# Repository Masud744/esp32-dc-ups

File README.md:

# esp32-dc-ups

> **Zero-Reboot DC UPS for ESP32 & IoT — Seamless 0ms power-path switching, wide DC input (6.5V–24V), 1S Li-ion battery backup, and dual regulated 5.0V & 3.3V outputs in KiCad.**

An industrial-grade, ultra-low-cost, uninterruptible power supply (DC UPS) module designed from the ground up to prevent brownout crashes and reboot loops on ESP32, ESP8266, Raspberry Pi Pico, and sensitive IoT sensor nodes. Designed in **KiCad 10** with 100% verified Design Rule Checks (DRC) and Electrical Rule Checks (ERC).

---

## 3D Hardware Previews

| Isometric View | Top View |
| :---: | :---: |
|  |  |

---

## Why esp32-dc-ups?

Most DIY IoT backup solutions connect a single 18650 lithium battery directly to an ESP32's `VIN` or rely on simple diode-ORing circuits. In production deployments, this leads to two major failure modes:

### 1. The "AMS1117 LDO Dropout Trap"
Over 90% of budget ESP32 development boards (NodeMCU-32S, ESP32-WROOM DevKit) use the **AMS1117-3.3** linear regulator, which has a dropout voltage ($V_{drop}$) of **$1.1\text{V} - 1.3\text{V}$** under typical Wi-Fi transmission bursts ($300\text{mA} - 500\text{mA}$):
$$V_{IN(min)} = 3.3\text{V} + 1.1\text{V} = 4.4\text{V}$$
* A standard single-cell Li-ion battery discharges from **$4.2\text{V} \rightarrow 3.0\text{V}$** (nominal $3.7\text{V}$).
* When battery voltage dips below $4.0\text{V}$, the AMS1117's output drops below $2.8\text{V}$, instantly tripping the ESP32 internal brownout detector (BOD) and causing infinite reboot loops.

### 2. Li-ion Charger Never Terminates
Powering an active IoT microcontroller directly across a charging TP4056 module causes continuous load current ($>70\text{mA}$) to draw through the battery pins. The TP4056 never detects the $C/10$ termination threshold, causing perpetual float charging, battery swelling, plating, and thermal hazards.

### The Solution: True 3-Stage Isolated Power-Path

| Feature | Standard USB / Diode ORing | Commercial Power Banks | **esp32-dc-ups (This Project)** |
| :--- | :---: | :---: | :---: |
| **Switchover Delay** | $>10\text{ms}$ (Reboots ESP) | $50\text{ms} - 200\text{ms}$ (Full Reboot) | **$0\text{ms}$ (Zero Delay, Anti-Reboot)** |
| **Input Voltage Range** | $5.0\text{V} \pm 5\%$ only | $5.0\text{V}$ only | **$6.5\text{V} - 24.0\text{V}$ Wide DC** |
| **Reverse Polarity Protection** | Rare / None | Fuse / None | **1N5822 3A Schottky Protected** |
| **Li-ion Termination ($C/10$)** | Broken (Continuous load) | Internal BMS | **Fully Isolated (Load never touches battery during mains)** |
| **Dual Regulated Rails** | No | 5V only | **5.0V (Boost 2A) + 3.3V (LDO) on Screw Terminals** |
| **Build Cost** | BDT 300 | BDT 1,200 – 1,800 | **BDT 430 – 490 (~$4 USD)** |

---

## Key Features

1. **Wide DC Input Stage (6.5V – 24V):**
   - High-current 5.08mm screw terminal (`J1`).
   - Integrated reverse-polarity protection via **1N5822 (3A / 40V Schottky)**.
   - Dual-stage input filter with high-frequency decoupling ($100\mu\text{F} / 35\text{V} + 100\text{nF}$).
   - Steps down any standard adapter ($7.5\text{V}, 9\text{V}, 12\text{V}, 15\text{V}, 19\text{V}, 24\text{V}$) to a clean $5.0\text{V}$ bus via high-efficiency Buck converter headers.

2. **Isolated Safe Charging (TP4056 + DW01A):**
   - System load is completely isolated from the battery charging circuit during mains operation.
   - TP4056 properly reaches its $C/10$ charge cut-off ($4.20\text{V} \pm 1\%$), maximizing cell cycle life.
   - Compatible with any 1S $3.7\text{V}$ 18650 cylindrical cell or Li-Po pouch battery.

3. **Sub-Millisecond Zero-Delay Power-Path Switching:**
   - Active P-Channel MOSFET (**NDP6020P / AO3401**) + Ultra-Fast Dual Schottky Barrier Diode (**MBR460CT**).
   - $10\text{k}\Omega$ pull-down resistor ensures instantaneous gate turn-on when mains voltage drops.
   - Switched intermediate bus backed by a low-ESR bulk capacitance matrix ($220\mu\text{F} + 10\mu\text{F} + 100\text{nF}$) for **$0\text{ms}$ cutover transition**.

4. **Synchronous Dual Regulated Outputs:**
   - **5.0V Rail:** Regulated via MT3608 high-frequency boost converter with a massive **$1000\mu\text{F} / 25\text{V}$ reservoir capacitor** to easily absorb ESP32 Wi-Fi TX current spikes ($>450\text{mA}$).
   - **3.3V Rail:** Dedicated onboard **AMS1117-3.3** linear regulator with thermal via array connecting directly to the bottom solid ground plane.
   - Both rails terminate on dedicated 5.08mm Phoenix-compatible screw terminals.

---

## System Architecture

```
[DC IN 6.5V-24V] ──> [1N5822 Schottky] ──> [Input Buck Module] ──> [+5V_IN Bus]
  (Screw Term J1)      (Reverse Protect)      (Steps down to 5.0V)        │
                                                                         ├──> [TP4056 + DW01A] ──> [1S Li-ion Battery]
                                                                         │       (Isolated Charge)          │
                                                                         │                                  │
[MT3608 Boost 5.1V] <── [Zero-Delay P-MOSFET + MBR460CT Power-Path] <────┴──────────────────────────────────┘
        │
        ├───> [1000uF Reservoir Cap] ───> [5.0V OUT Screw Terminal (J6)]
        │
        └───> [AMS1117-3.3 LDO] ────────> [3.3V OUT Screw Terminal (J7)]
```

---

## Hardware Specifications

| Parameter | Specification | Note |
| :--- | :--- | :--- |
| **Input Voltage Range** | $6.5\text{V} - 24.0\text{V}$ DC | Compatible with 9V/12V/19V/24V adapters |
| **Backup Battery** | Single-cell Li-ion / Li-Po ($3.7\text{V}$ nom, $4.2\text{V}$ max) | 18650, 21700, or flat pouch cell |
| **Output 1 (5V Rail)** | $5.0\text{V} \pm 2\%$ @ up to $2.0\text{A}$ | Primary supply for dev kits, sensors, relays |
| **Output 2 (3.3V Rail)** | $3.3\text{V} \pm 1.5\%$ @ up to $800\text{mA}$ | Direct clean rail for ESP32 SoC, sensors |
| **Cutover Transition Delay** | **$< 0.1\text{ms}$ (Effectively 0ms)** | Microcontroller brownout risk: **0%** |
| **PCB Dimensions** | $105\text{mm} \times 70\text{mm}$ | 2-layer FR4, $1.6\text{mm}$ thickness, 1oz Cu |
| **Mounting Holes** | $4\times \text{M3}$ ($3.2\text{mm}$) | Grounded rings with thermal relief |
| **Terminals** | $3\times 5.08\text{mm}$ 2-Pin Screw Terminals | Phoenix MKDS-1,5/2-5.08 compatible |

---

## Pinout & Terminal Mapping

### Screw Terminals
* **`J1 (DC IN)`**:
  - `Pin 1 (+)`: DC Input Positive ($+6.5\text{V} - 24\text{V}$)
  - `Pin 2 (-)`: System Common Ground (`GND`)
* **`J6 (5V OUT)`**:
  - `Pin 1 (+)`: Regulated $+5.0\text{V}$ Output
  - `Pin 2 (-)`: System Common Ground (`GND`)
* **`J7 (3.3V OUT)`**:
  - `Pin 1 (+)`: Regulated $+3.3\text{V}$ Output
  - `Pin 2 (-)`: System Common Ground (`GND`)

### Module Header Interfaces (2.54mm Pitch)
* **`J_B_IN`**: To Step-Down Buck Converter Input (`Pin 1: +VIN_FILT`, `Pin 2: GND`)
* **`J_B_OUT`**: From Step-Down Buck Converter Output (`Pin 1: +5V_IN`, `Pin 2: GND`)
* **`J2`**: To TP4056 Charger Input (`Pin 1: +5V_IN`, `Pin 2: GND`)
* **`J3`**: From TP4056 / Battery Protection Board Output (`Pin 1: V_BAT_PROT`, `Pin 2: GND`)
* **`J4`**: To MT3608 Boost Converter Input (`Pin 1: V_SW`, `Pin 2: GND`)
* **`J5`**: From MT3608 Boost Converter Output (`Pin 1: +5V_OUT`, `Pin 2: GND`)

---

## Bill of Materials (BOM) & Budget Analysis

All components were intentionally selected for ready availability in local electronics markets (Dhaka Patuatuli / Elephant Road, TechShopBD, RoboticsBD, Daraz BD):

| Item | Component | Package / Rating | Qty | Est. Cost (BDT) | Purpose |
| :---: | :--- | :--- | :---: | :---: | :--- |
| 1 | **Buck Converter Module** | Mini-360 / LM2596 / MP1584 | 1 | ৳ 45 – 65 | Steps down 6.5V–24V to 5V |
| 2 | **TP4056 Charger Module** | Type-C with DW01A + 8205A | 1 | ৳ 25 – 35 | Safe 1S CC/CV charging with protection |
| 3 | **MT3608 Boost Module** | 2A DC-DC Step-Up | 1 | ৳ 35 – 45 | Regulates switched bus to 5.1V |
| 4 | **MBR460CT / MBR1045** | TO-220 Dual Schottky Diode | 1 | ৳ 20 – 30 | Mains power-path steering |
| 5 | **NDP6020P / AO3401** | TO-220 / SOT-23 P-MOSFET | 1 | ৳ 25 – 35 | Battery power-path switch |
| 6 | **AMS1117-3.3** | SOT-223 Low-Dropout Regulator | 1 | ৳ 10 – 15 | Dedicated 3.3V output rail |
| 7 | **1N5822** | DO-201AD 3A Schottky Diode | 1 | ৳ 8 – 12 | Input reverse polarity protection |
| 8 | **1000uF 25V** | Radial Electrolytic Capacitor | 1 | ৳ 12 – 18 | High-capacity output buffer |
| 9 | **220uF 16V** | Radial Electrolytic Capacitor | 2 | ৳ 10 – 16 | Input & switched bus smoothing |
| 10 | **10uF, 22uF, 100uF** | Radial Capacitors | 4 | ৳ 15 – 20 | LDO & rail decoupling |
| 11 | **100nF (104)** | Multilayer Ceramic Capacitor | 5 | ৳ 5 – 10 | High-frequency noise suppression |
| 12 | **10kΩ Resistor** | 1/4W Through-Hole | 1 | ৳ 1 – 2 | MOSFET gate pull-down |
| 13 | **5.08mm Screw Terminals** | 2-Pin Terminal Blocks | 3 | ৳ 30 – 45 | DC IN, 5V OUT, 3.3V OUT |
| 14 | **2.54mm Pin Headers** | Male / Female strip | 1 | ৳ 10 – 15 | Sub-module interconnects |
| 15 | **Custom 2-Layer PCB** | 105mm × 70mm FR4 | 1 | ৳ 120 – 150 | Local fabrication batch price |
| **Total** | | | | **৳ 371 – 513** | **~$3.50 – $4.80 USD** |

---

## Verification & Design Rule Checks

The project includes verified verification logs generated via the KiCad CLI test suite:

- **Electrical Rules Check (ERC):** Passed with **0 errors, 0 unconnected wires**.
- **Design Rules Check (DRC):** Passed with **0 violations, 0 unconnected pads, 0 footprint errors**.
- **Reports:**
  - Official DRC Report: [`exports/drc_report.rpt`](exports/drc_report.rpt)
  - Official ERC Report: [`exports/erc_report.rpt`](exports/erc_report.rpt)

---

## Repository Structure

```text
esp32-dc-ups/
├── kicad/                             # KiCad 10 project and schematic files
│   ├── DC_UPS_IoT.kicad_pro           # KiCad Project File
│   ├── DC_UPS_IoT.kicad_sch           # Complete Schematic
│   ├── DC_UPS_IoT.kicad_pcb           # 2-Layer PCB Layout
│   └── DC_UPS_IoT.kicad_prl           # Project Local Configuration
│
├── exports/                           # High-resolution production renders & reports
│   ├── DC_UPS_IoT_3d_iso.png          # 3D Isometric Board Render
│   ├── DC_UPS_IoT_3d_top.png          # 3D Top-Down Board Render
│   ├── DC_UPS_IoT.svg                 # Schematic Diagram (Vector SVG)
│   ├── DC_UPS_IoT_pcb.svg             # PCB Copper & Silk (Vector SVG)
│   ├── drc_report.rpt                 # Verified DRC Report (0 violations)
│   └── erc_report.rpt                 # Verified ERC Report (0 errors)
│
├── simulation/                        # Automation & SPICE transient simulation
│   ├── build_pcb.py                   # PCB Generation & Layout Automation
│   ├── build_kicad_project.py         # KiCad Schematic Generation Script
│   ├── simulate_ups.py                # Python/SciPy Transient Cutover Simulation
│   ├── generate_sim_files.py          # LTspice & Falstad Netlist Generator
│   ├── dc_ups_ltspice.cir             # LTspice Circuit Model
│   ├── falstad_circuit.txt            # Falstad Interactive Circuit Data
│   ├── falstad_link.txt               # Direct Falstad Web Simulator Link
│   └── ups_transient_simulation.png   # Transient Waveform Plot
│
├── visual_breadboard_interactive.html # Interactive visual wiring guide
├── .gitignore                         # KiCad temporary & lock file ignore rules
├── LICENSE                            # MIT Open Source License
└── README.md                          # Project Documentation
```

---

## Getting Started in KiCad

1. Clone this repository:
   ```bash
   git clone https://github.com/Masud744/esp32-dc-ups.git
   cd esp32-dc-ups
   ```
2. Open KiCad 8 or KiCad 10.
3. Select **File -> Open Project...** and choose:
   ```text
   kicad/DC_UPS_IoT.kicad_pro
   ```
4. **Interactive 3D Viewer:**
   Open the PCB Editor (`DC_UPS_IoT.kicad_pcb`) and press **`Alt + 3`** to inspect the fully rendered 3D PCB model.

---

## Author

**Shahriar Alom Masud**  
B.Sc. Engg. in IoT & Robotics Engineering  
University of Frontier Technology, Bangladesh  
Email: [masud.nil74@gmail.com](mailto:masud.nil74@gmail.com)  
GitHub: [@Masud744](https://github.com/Masud744) | LinkedIn: [linkedin.com/in/shahriar-alom-masud](https://www.linkedin.com/in/shahriar-alom-masud)

---

## License

This project is open-source hardware licensed under the **MIT License**. See [LICENSE](LICENSE) for full details.

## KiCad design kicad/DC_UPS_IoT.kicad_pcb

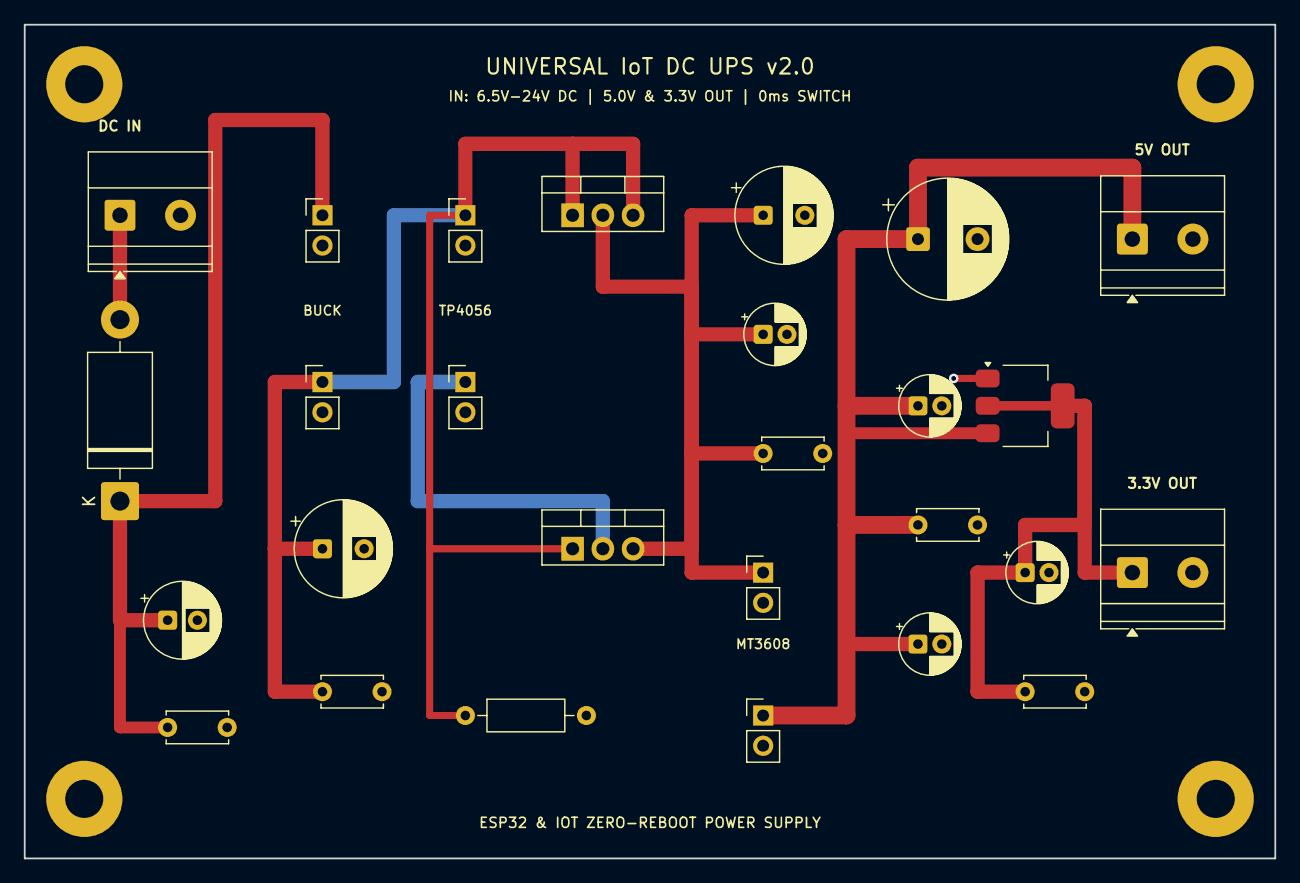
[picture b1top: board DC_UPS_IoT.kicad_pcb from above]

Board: 2 copper layers, 105.0 x 70.0 mm, 31 parts (0 on the bottom side), 8 nets.

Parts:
C1: 220uF_16V; CP_Radial_D8.0mm_P3.50mm
C2, C5, C7: 10uF_16V; CP_Radial_D5.0mm_P2.00mm
C3, C6, C9: 100nF; C_Disc_D5.0mm_W2.5mm_P5.00mm
C4: 1000uF_25V; CP_Radial_D10.0mm_P5.00mm
C8: 22uF_10V; CP_Radial_D5.0mm_P2.00mm
C_B1: 220uF_16V; CP_Radial_D8.0mm_P3.50mm
C_B2: 100nF; C_Disc_D5.0mm_W2.5mm_P5.00mm
C_IN1: 100uF_35V; CP_Radial_D6.3mm_P2.50mm
C_IN2: 100nF; C_Disc_D5.0mm_W2.5mm_P5.00mm
D1: MBR460CT; TO-220-3_Vertical
D_REV: 1N5822; D_DO-201AD_P15.24mm_Horizontal
H1, H2, H3, H4: M3; MountingHole_3.2mm_M3_Pad
J1: DC_IN; TerminalBlock_Phoenix_MKDS-1,5-2-5.08_1x02_P5.08mm_Horizont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
J2: TO_TP4056_IN; PinHeader_1x02_P2.54mm_Vertical
J3: FROM_TP4056_OUT; PinHeader_1x02_P2.54mm_Vertical
J4: TO_MT3608_IN; PinHeader_1x02_P2.54mm_Vertical
J5: FROM_MT3608_OUT; PinHeader_1x02_P2.54mm_Vertical
J6: 5V_OUT; TerminalBlock_Phoenix_MKDS-1,5-2-5.08_1x02_P5.08mm_Horizont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
J7: 3V3_OUT; TerminalBlock_Phoenix_MKDS-1,5-2-5.08_1x02_P5.08mm_Horizont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
J_B_IN: TO_BUCK_IN; PinHeader_1x02_P2.54mm_Vertical
J_B_OUT: FROM_BUCK_OUT; PinHeader_1x02_P2.54mm_Vertical
Q1: NDP6020P; TO-220-3_Vertical
R1: 10k; R_Axial_DIN0207_L6.3mm_D2.5mm_P10.16mm_Horizontal
U1: AMS1117-3.3; SOT-223-3_TabPin2

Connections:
+3V3_OUT: C8.1, C9.1, J7.1, U1.2
+5V_IN: C_B1.1, C_B2.1, D1.1, D1.3, J2.1, J_B_OUT.1, Q1.1, R1.1
+5V_OUT: C4.1, C5.1, C6.1, C7.1, J5.1, J6.1, U1.3
+VIN_FILT: C_IN1.1, C_IN2.1, D_REV.1, J_B_IN.1
+VIN_RAW: D_REV.2, J1.1
GND: C1.2, C2.2, C3.2, C4.2, C5.2, C6.2, C7.2, C8.2, C9.2, C_B1.2, C_B2.2, C_IN1.2, C_IN2.2, H1.1, H2.1, H3.1, H4.1, J1.2, J2.2, J3.2, J4.2, J5.2, J6.2, J7.2, J_B_IN.2, J_B_OUT.2, R1.2, U1.1
V_BAT_PROT: J3.1, Q1.2
V_SW: C1.1, C2.1, C3.1, D1.2, J4.1, Q1.3
